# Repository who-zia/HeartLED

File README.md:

# HeartLED
> a simple blinking led tbfh
---
#### Pictures!
|  |  |

|  |  |

|   |  |

--

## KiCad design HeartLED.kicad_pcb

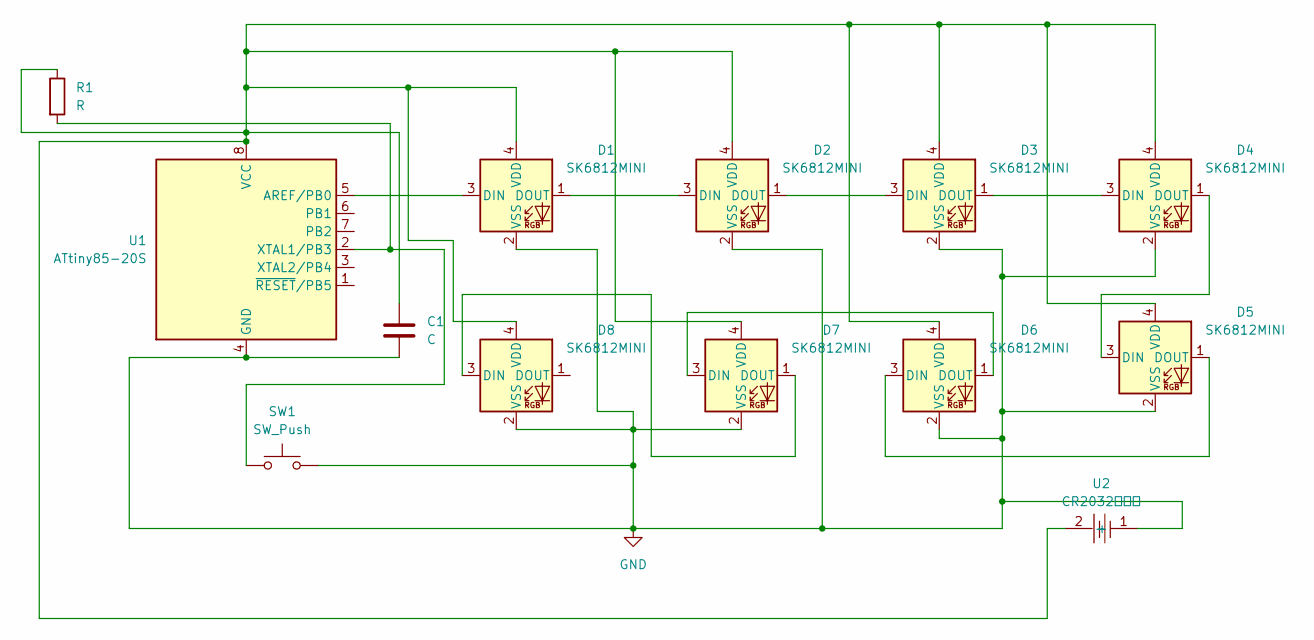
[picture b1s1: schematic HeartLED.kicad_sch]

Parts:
C1: C; C_0805_2012Metric
D1, D2, D3, D4, D5, D6, D7, D8: SK6812MINI; LED_SK6812MINI_PLCC4_3.5x3.5mm_P1.75mm
R1: R; R_0805_2012Metric
SW1: SW_Push; SW_SPST_PTS645Sx43SMTR92
U1: ATtiny85-20S; SOIC-8_5.3x5.3mm_P1.27mm
U2: CR2032电池座; BatteryHolder_Keystone_3034_1x20mm; MPN CR2032电池座; LCSC Part C9900016310

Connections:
GND: C1.2, D1.2 (VSS), D2.2 (VSS), D3.2 (VSS), D4.2 (VSS), D5.2 (VSS), D6.2 (VSS), D7.2 (VSS), D8.2 (VSS), SW1.2, U1.4 (GND), U2.1 (-)
unnamed: D1.3 (DIN), U1.5 (AREF/PB0)
unnamed: D1.1 (DOUT), D2.3 (DIN)
unnamed: C1.1, D1.4 (VDD), D2.4 (VDD), D3.4 (VDD), D4.4 (VDD), D5.4 (VDD), D6.4 (VDD), D7.4 (VDD), D8.4 (VDD), R1.1, U1.8 (VCC), U2.2 (+)
unnamed: D2.1 (DOUT), D3.3 (DIN)
unnamed: D3.1 (DOUT), D4.3 (DIN)
unnamed: D4.1 (DOUT), D5.3 (DIN)
unnamed: D5.1 (DOUT), D6.3 (DIN)
unnamed: D6.1 (DOUT), D7.3 (DIN)
unnamed: D7.1 (DOUT), D8.3 (DIN)
unnamed: R1.2, SW1.1, U1.2 (XTAL1/PB3)

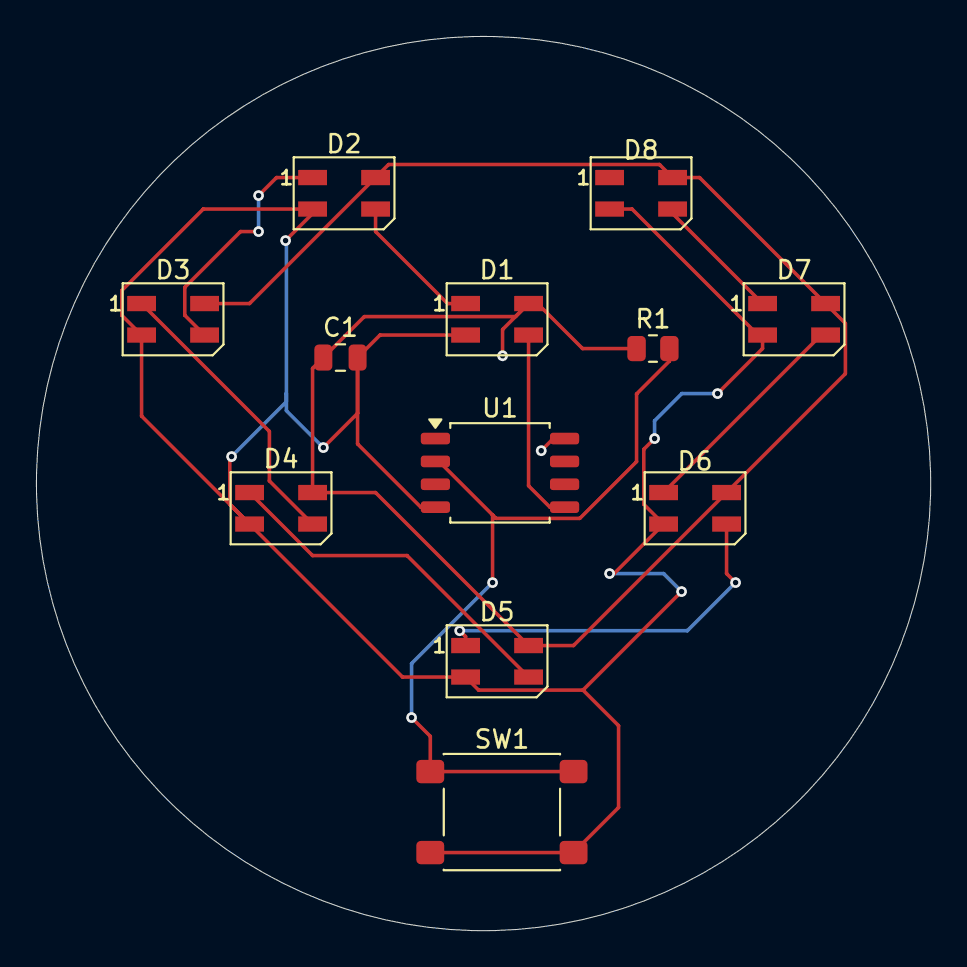
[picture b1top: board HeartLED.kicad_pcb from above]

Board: 2 copper layers, 49.7 x 49.7 mm, 13 parts (1 on the bottom side), 11 nets.
